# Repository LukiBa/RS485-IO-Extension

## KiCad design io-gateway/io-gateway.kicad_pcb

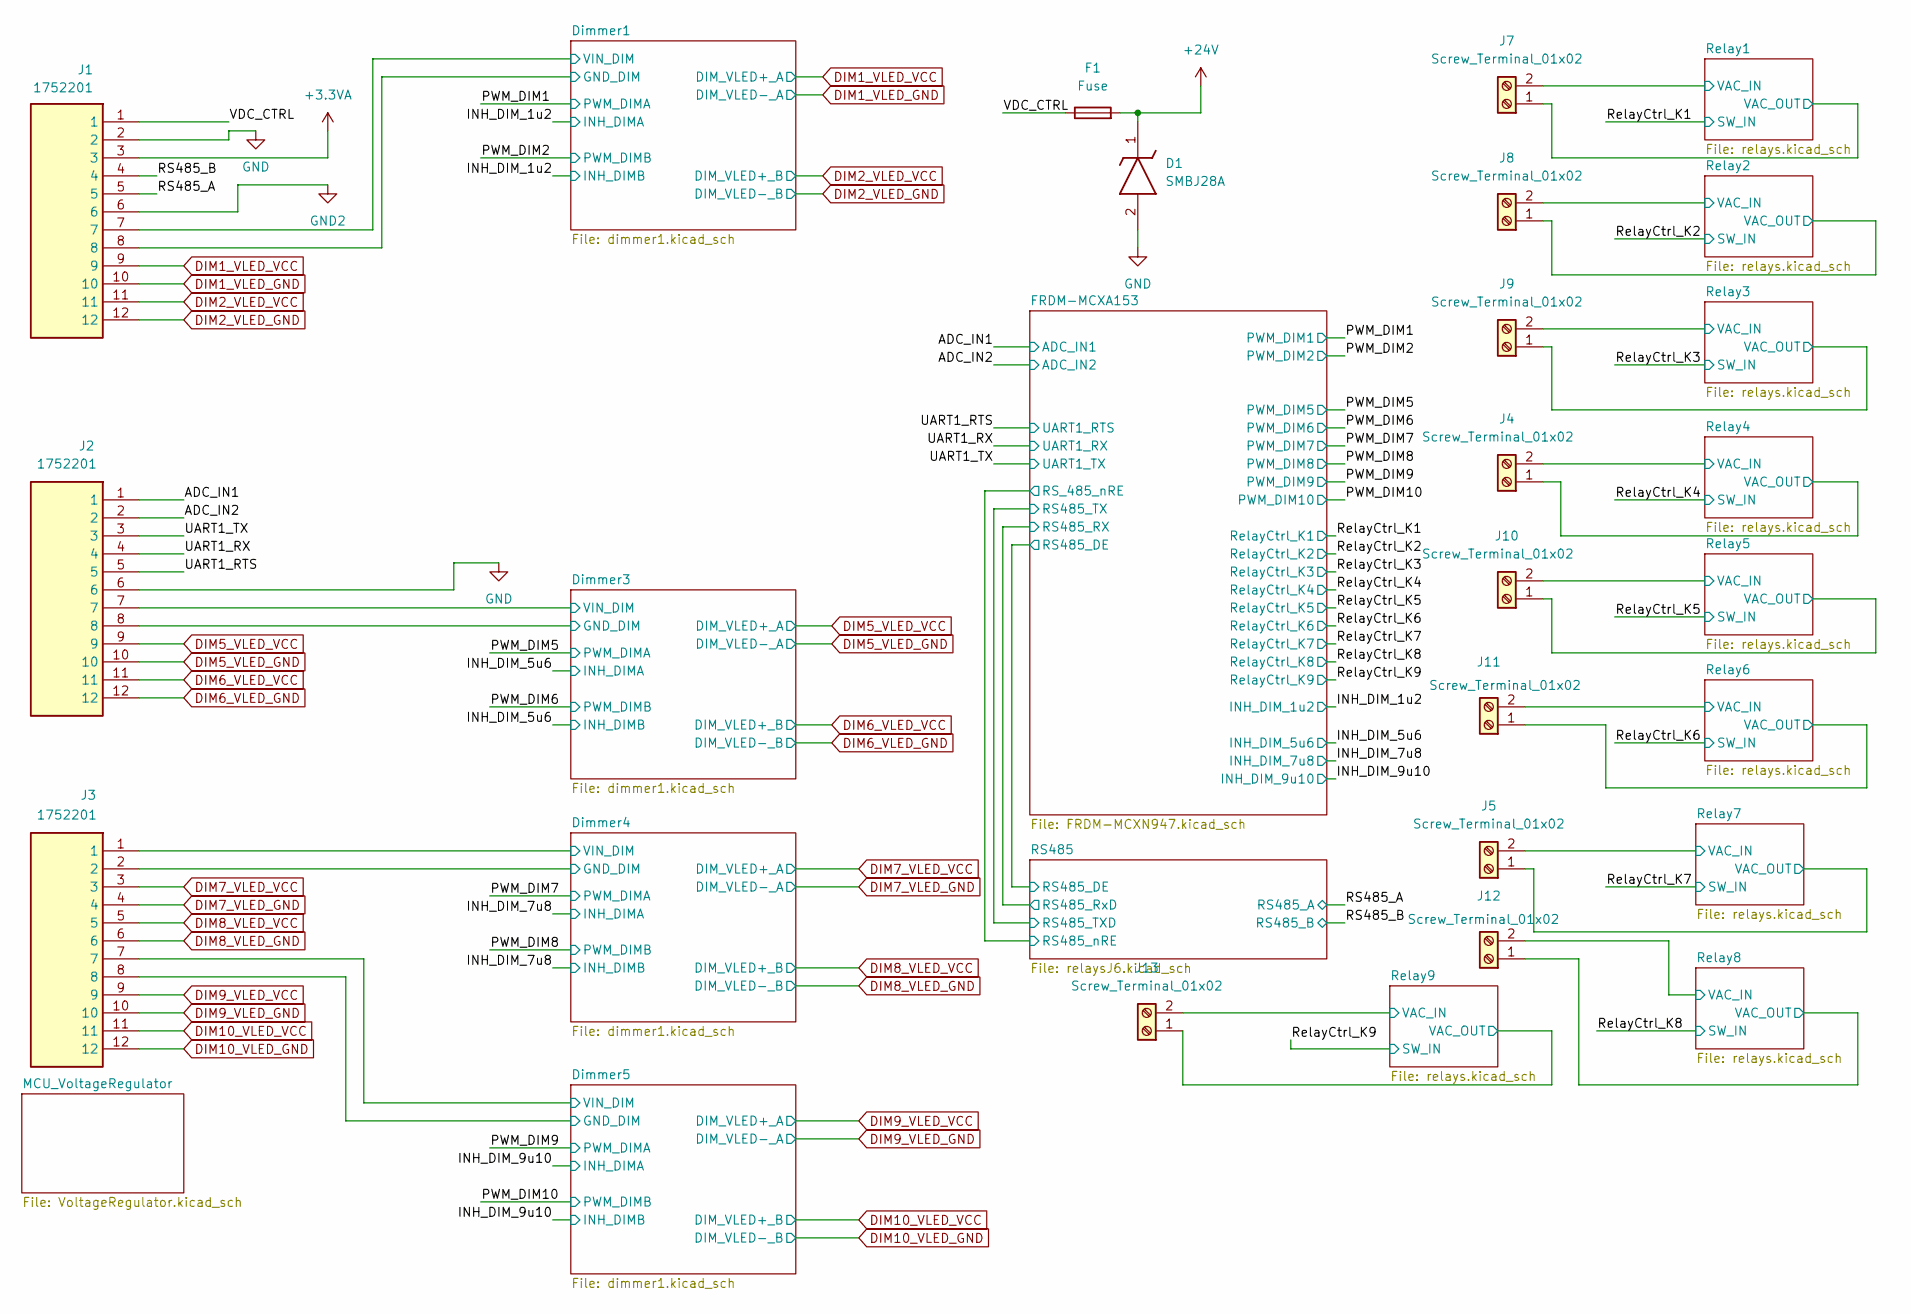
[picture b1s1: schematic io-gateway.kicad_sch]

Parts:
D1: SMBJ28A; DIOM5436X244N; Mouser Part Number 652-SMBJ28A
F1: Fuse; Fuse_1206_3216Metric_Pad1.42x1.75mm_HandSolder
J1, J2, J3: 1752201; Mouser Part Number 651-1752201
J4, J5, J7, J8, J9, J10, J11, J12, J13: Screw_Terminal_01x02; TerminalBlock_MaiXu_MX126-5.0-02P_1x02_P5.00mm

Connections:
+3.3VA: J1.3; also elsewhere on the board
+24V: D1.1 (K), F1.2; also elsewhere on the board
/ADC_IN1: J2.1; also elsewhere on the board
/ADC_IN2: J2.2; also elsewhere on the board
/Dimmer1/VIN_DIM: J1.7; also elsewhere on the board
/Dimmer3/VIN_DIM: J2.7; also elsewhere on the board
/Dimmer4/VIN_DIM: J3.1; also elsewhere on the board
/Dimmer5/VIN_DIM: J3.7; also elsewhere on the board
/RS485_A: J1.5; also elsewhere on the board
/RS485_B: J1.4; also elsewhere on the board
/Relay1/VAC_IN: J7.2; also elsewhere on the board
/Relay1/VAC_OUT: J7.1; also elsewhere on the board
/Relay2/VAC_IN: J8.2; also elsewhere on the board
/Relay2/VAC_OUT: J8.1; also elsewhere on the board
/Relay3/VAC_IN: J9.2; also elsewhere on the board
/Relay3/VAC_OUT: J9.1; also elsewhere on the board
/Relay4/VAC_IN: J4.2; also elsewhere on the board
/Relay4/VAC_OUT: J4.1; also elsewhere on the board
/Relay5/VAC_IN: J10.2; also elsewhere on the board
/Relay5/VAC_OUT: J10.1; also elsewhere on the board
/Relay6/VAC_IN: J11.2; also elsewhere on the board
/Relay6/VAC_OUT: J11.1; also elsewhere on the board
/Relay7/VAC_IN: J5.2; also elsewhere on the board
/Relay7/VAC_OUT: J5.1; also elsewhere on the board
/Relay8/VAC_IN: J12.2; also elsewhere on the board
/Relay8/VAC_OUT: J12.1; also elsewhere on the board
/Relay9/VAC_IN: J13.2; also elsewhere on the board
/Relay9/VAC_OUT: J13.1; also elsewhere on the board
/UART1_RTS: J2.5; also elsewhere on the board
/UART1_RX: J2.4; also elsewhere on the board
/UART1_TX: J2.3; also elsewhere on the board
/VDC_CTRL: F1.1, J1.1
DIM1_VLED_GND: J1.10; also elsewhere on the board
DIM1_VLED_VCC: J1.9; also elsewhere on the board
DIM2_VLED_GND: J1.12; also elsewhere on the board
DIM2_VLED_VCC: J1.11; also elsewhere on the board
DIM5_VLED_GND: J2.10; also elsewhere on the board
DIM5_VLED_VCC: J2.9; also elsewhere on the board
DIM6_VLED_GND: J2.12; also elsewhere on the board
DIM6_VLED_VCC: J2.11; also elsewhere on the board
DIM7_VLED_GND: J3.4; also elsewhere on the board
DIM7_VLED_VCC: J3.3; also elsewhere on the board
DIM8_VLED_GND: J3.6; also elsewhere on the board
DIM8_VLED_VCC: J3.5; also elsewhere on the board
DIM9_VLED_GND: J3.10; also elsewhere on the board
DIM9_VLED_VCC: J3.9; also elsewhere on the board
DIM10_VLED_GND: J3.12; also elsewhere on the board
DIM10_VLED_VCC: J3.11; also elsewhere on the board
GND: D1.2 (A), J1.2, J1.8, J2.6, J2.8, J3.2, J3.8; also elsewhere on the board
GND2: J1.6; also elsewhere on the board

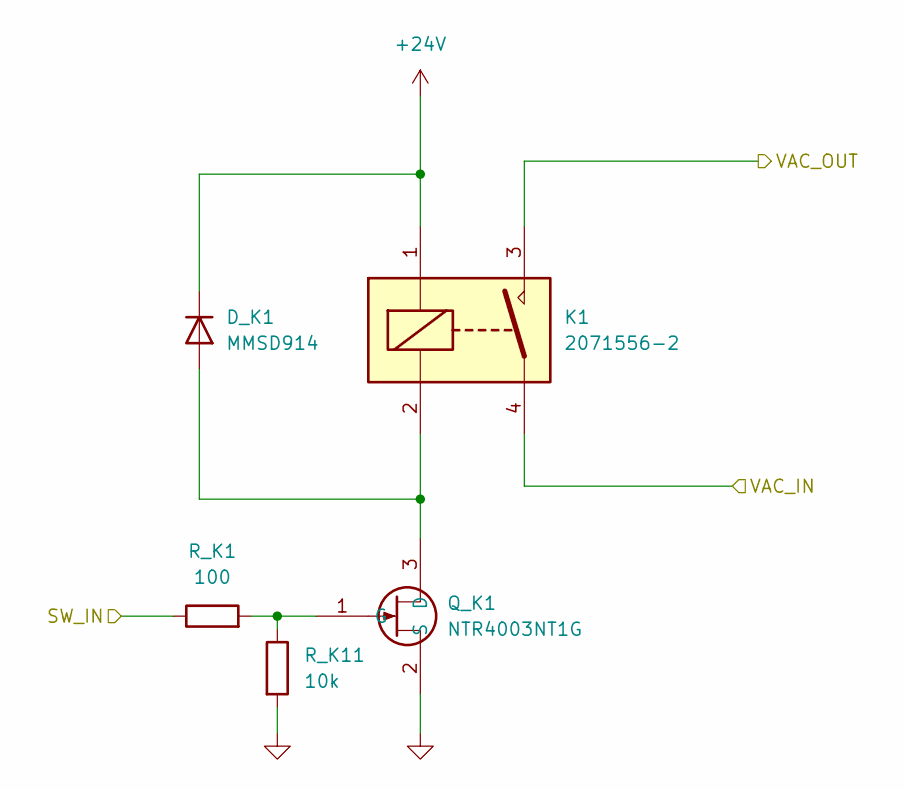
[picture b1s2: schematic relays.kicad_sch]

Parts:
D_K1: MMSD914; D_SOD-123
K1: 2071556-2; 20715562; Mouser Part Number 655-2071556-2
Q_K1: NTR4003NT1G; SOT-23-3; Mouser Part Number 863-NTR4003NT1G
R_K1: 100; R_0603_1608Metric_Pad0.98x0.95mm_HandSolder
R_K11: 10k; R_0603_1608Metric_Pad0.98x0.95mm_HandSolder

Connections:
+24V: D_K1.1 (K), K1.1 (COIL_1); also elsewhere on the board
/Relay1/VAC_IN: K1.4 (NO); also elsewhere on the board
/Relay1/VAC_OUT: K1.3 (COM); also elsewhere on the board
/RelayCtrl_K1: R_K1.1; also elsewhere on the board
GND: Q_K1.2 (S), R_K11.2; also elsewhere on the board
unnamed: D_K1.2 (A), K1.2 (COIL_2), Q_K1.3 (D)
unnamed: Q_K1.1 (G), R_K1.2, R_K11.1

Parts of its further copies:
D_K2, D_K3, D_K4, D_K5, D_K6, D_K7, D_K8, D_K9: MMSD914; D_SOD-123
K2, K3, K4, K5, K6, K7, K8, K9: 2071556-2; 20715562; Mouser Part Number 655-2071556-2
Q_K2, Q_K3, Q_K4, Q_K5, Q_K6, Q_K7, Q_K8, Q_K9: NTR4003NT1G; SOT-23-3; Mouser Part Number 863-NTR4003NT1G
R_K2, R_K3, R_K4, R_K5, R_K6, R_K7, R_K8, R_K9: 100; R_0603_1608Metric_Pad0.98x0.95mm_HandSolder
R_K12, R_K13, R_K14, R_K15, R_K16, R_K17, R_K18, R_K19: 10k; R_0603_1608Metric_Pad0.98x0.95mm_HandSolder

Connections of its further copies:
+24V: D_K2.1 (K), D_K3.1 (K), D_K4.1 (K), D_K5.1 (K), D_K6.1 (K), D_K7.1 (K), D_K8.1 (K), D_K9.1 (K), K2.1 (COIL_1), K3.1 (COIL_1), K4.1 (COIL_1), K5.1 (COIL_1), K6.1 (COIL_1), K7.1 (COIL_1), K8.1 (COIL_1), K9.1 (COIL_1); also elsewhere on the board
/Relay2/VAC_IN: K2.4 (NO); also elsewhere on the board
/Relay2/VAC_OUT: K2.3 (COM); also elsewhere on the board
/Relay3/VAC_IN: K3.4 (NO); also elsewhere on the board
/Relay3/VAC_OUT: K3.3 (COM); also elsewhere on the board
/Relay4/VAC_IN: K4.4 (NO); also elsewhere on the board
/Relay4/VAC_OUT: K4.3 (COM); also elsewhere on the board
/Relay5/VAC_IN: K5.4 (NO); also elsewhere on the board
/Relay5/VAC_OUT: K5.3 (COM); also elsewhere on the board
/Relay6/VAC_IN: K6.4 (NO); also elsewhere on the board
/Relay6/VAC_OUT: K6.3 (COM); also elsewhere on the board
/Relay7/VAC_IN: K7.4 (NO); also elsewhere on the board
/Relay7/VAC_OUT: K7.3 (COM); also elsewhere on the board
/Relay8/VAC_IN: K8.4 (NO); also elsewhere on the board
/Relay8/VAC_OUT: K8.3 (COM); also elsewhere on the board
/Relay9/VAC_IN: K9.4 (NO); also elsewhere on the board
/Relay9/VAC_OUT: K9.3 (COM); also elsewhere on the board
/RelayCtrl_K2: R_K2.1; also elsewhere on the board
/RelayCtrl_K3: R_K3.1; also elsewhere on the board
/RelayCtrl_K4: R_K4.1; also elsewhere on the board
/RelayCtrl_K5: R_K5.1; also elsewhere on the board
/RelayCtrl_K6: R_K6.1; also elsewhere on the board
/RelayCtrl_K7: R_K7.1; also elsewhere on the board
/RelayCtrl_K8: R_K8.1; also elsewhere on the board
/RelayCtrl_K9: R_K9.1; also elsewhere on the board
GND: Q_K2.2 (S), Q_K3.2 (S), Q_K4.2 (S), Q_K5.2 (S), Q_K6.2 (S), Q_K7.2 (S), Q_K8.2 (S), Q_K9.2 (S), R_K12.2, R_K13.2, R_K14.2, R_K15.2, R_K16.2, R_K17.2, R_K18.2, R_K19.2; also elsewhere on the board
unnamed: D_K2.2 (A), K2.2 (COIL_2), Q_K2.3 (D)
unnamed: D_K3.2 (A), K3.2 (COIL_2), Q_K3.3 (D)
unnamed: D_K4.2 (A), K4.2 (COIL_2), Q_K4.3 (D)
unnamed: D_K5.2 (A), K5.2 (COIL_2), Q_K5.3 (D)
unnamed: D_K6.2 (A), K6.2 (COIL_2), Q_K6.3 (D)
unnamed: D_K7.2 (A), K7.2 (COIL_2), Q_K7.3 (D)
unnamed: D_K8.2 (A), K8.2 (COIL_2), Q_K8.3 (D)
unnamed: D_K9.2 (A), K9.2 (COIL_2), Q_K9.3 (D)
unnamed: Q_K2.1 (G), R_K2.2, R_K12.1
unnamed: Q_K3.1 (G), R_K3.2, R_K13.1
unnamed: Q_K4.1 (G), R_K4.2, R_K14.1
unnamed: Q_K5.1 (G), R_K5.2, R_K15.1
unnamed: Q_K6.1 (G), R_K6.2, R_K16.1
unnamed: Q_K7.1 (G), R_K7.2, R_K17.1
unnamed: Q_K8.1 (G), R_K8.2, R_K18.1
unnamed: Q_K9.1 (G), R_K9.2, R_K19.1

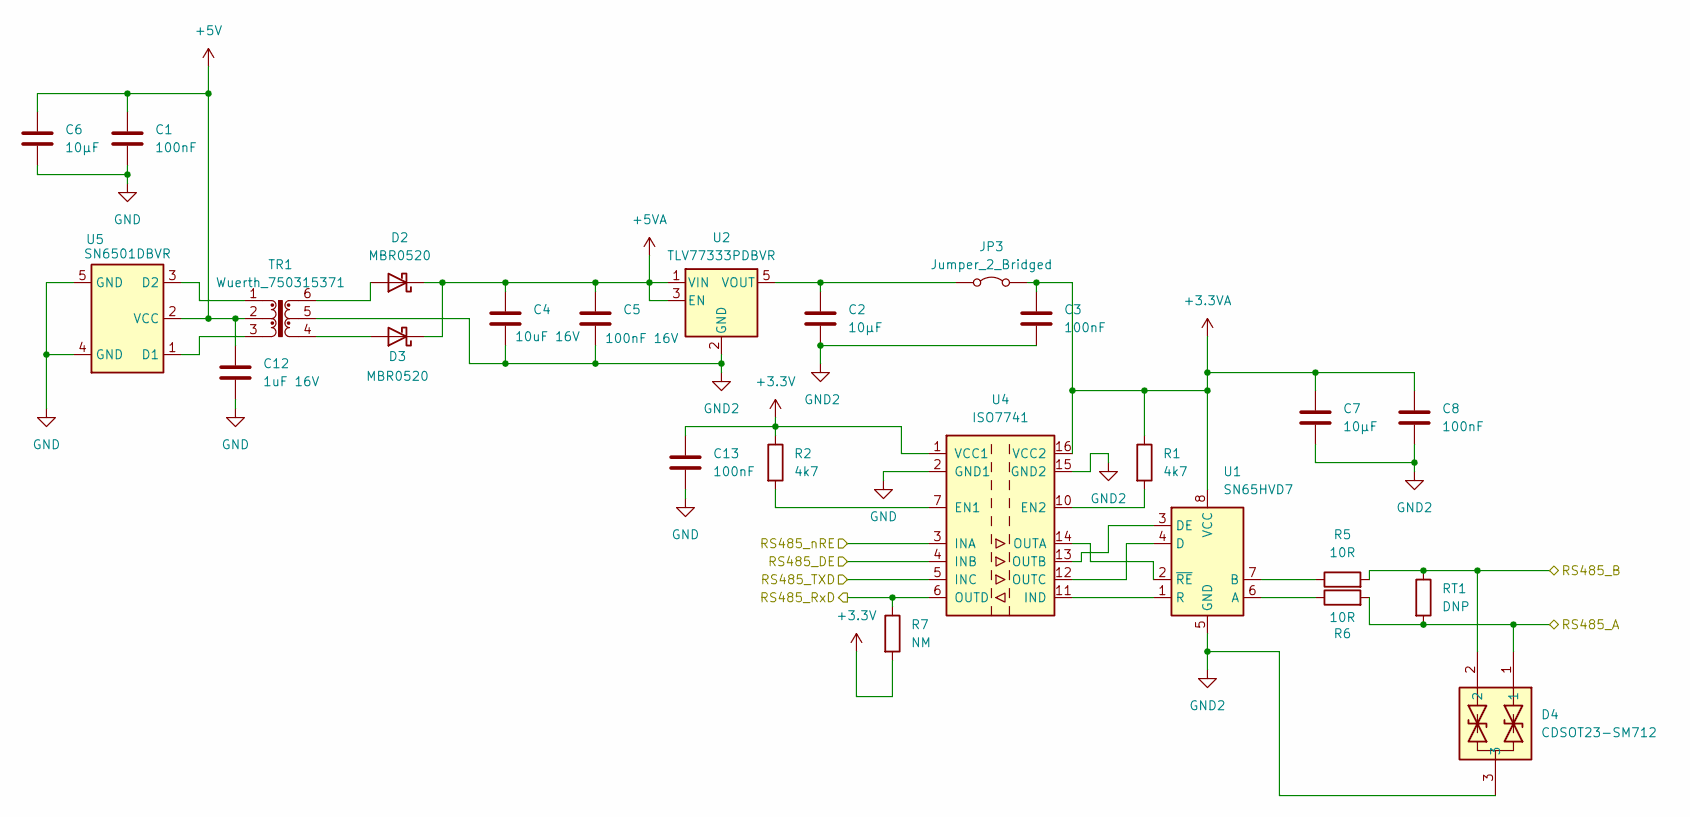
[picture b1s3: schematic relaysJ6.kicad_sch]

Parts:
C1, C3, C8, C13: 100nF; C_0603_1608Metric_Pad1.08x0.95mm_HandSolder
C2, C6, C7: 10µF; C_0603_1608Metric_Pad1.08x0.95mm_HandSolder
C4: 10uF 16V; C_0603_1608Metric_Pad1.08x0.95mm_HandSolder
C5: 100nF 16V; C_0603_1608Metric_Pad1.08x0.95mm_HandSolder
C12: 1uF 16V; C_0603_1608Metric_Pad1.08x0.95mm_HandSolder
D2, D3: MBR0520; D_SOD-123
D4: CDSOT23-SM712; SOT95P230X117-3N; Mouser Part Number 652-CDSOT23-SM712
JP3: Jumper_2_Bridged; PinHeader_1x02_P2.54mm_Vertical
R1, R2: 4k7; R_0603_1608Metric_Pad0.98x0.95mm_HandSolder
R5, R6: 10R; R_0603_1608Metric_Pad0.98x0.95mm_HandSolder
R7: NM; R_0603_1608Metric_Pad0.98x0.95mm_HandSolder
RT1: DNP; R_0603_1608Metric_Pad0.98x0.95mm_HandSolder
TR1: Wuerth_750315371; Transformer_Wuerth_750315371
U1: SN65HVD7; SOIC-8_3.9x4.9mm_P1.27mm
U2: TLV77333PDBVR; SOT-23-5
U4: ISO7741; SOIC-16W_7.5x10.3mm_P1.27mm
U5: SN6501DBVR; SOT-23-5

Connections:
+3.3V: C13.1, R2.1, R7.2, U4.1 (VCC1); also elsewhere on the board
+3.3VA: C3.1, C7.1, C8.1, JP3.2 (B), R1.1, U1.8 (VCC), U4.16 (VCC2); also elsewhere on the board
+5V: C1.1, C6.1, C12.1, TR1.2, U5.2 (VCC); also elsewhere on the board
+5VA: C4.1, C5.1, D2.1 (K), D3.1 (K), U2.1 (VIN), U2.3 (EN)
/FRDM-MCXA153/RS485_DE: U4.4 (INB); also elsewhere on the board
/FRDM-MCXA153/RS485_RX: R7.1, U4.6 (OUTD); also elsewhere on the board
/FRDM-MCXA153/RS485_TX: U4.5 (INC); also elsewhere on the board
/FRDM-MCXA153/RS_485_nRE: U4.3 (INA); also elsewhere on the board
/RS485_A: D4.1, R6.2, RT1.2; also elsewhere on the board
/RS485_B: D4.2, R5.2, RT1.1; also elsewhere on the board
GND: C1.2, C6.2, C12.2, C13.2, U4.2 (GND1), U4.8 (GND1), U5.4 (GND), U5.5 (GND); also elsewhere on the board
GND2: C2.2, C3.2, C4.2, C5.2, C7.2, C8.2, D4.3, TR1.5, U1.5 (GND), U2.2 (GND), U4.9 (GND2), U4.15 (GND2); also elsewhere on the board
unnamed: D2.2 (A), TR1.6
unnamed: D3.2 (A), TR1.4
unnamed: C2.1, JP3.1 (A), U2.5 (VOUT)
unnamed: R6.1, U1.6 (A)
unnamed: R5.1, U1.7 (B)
unnamed: U1.4 (D), U4.12 (OUTC)
unnamed: U1.3 (DE), U4.13 (OUTB)
unnamed: U1.1 (R), U4.11 (IND)
unnamed: U1.2 (~RE), U4.14 (OUTA)
unnamed: R2.2, U4.7 (EN1)
unnamed: R1.2, U4.10 (EN2)
unnamed: TR1.3, U5.1 (D1)
unnamed: TR1.1, U5.3 (D2)

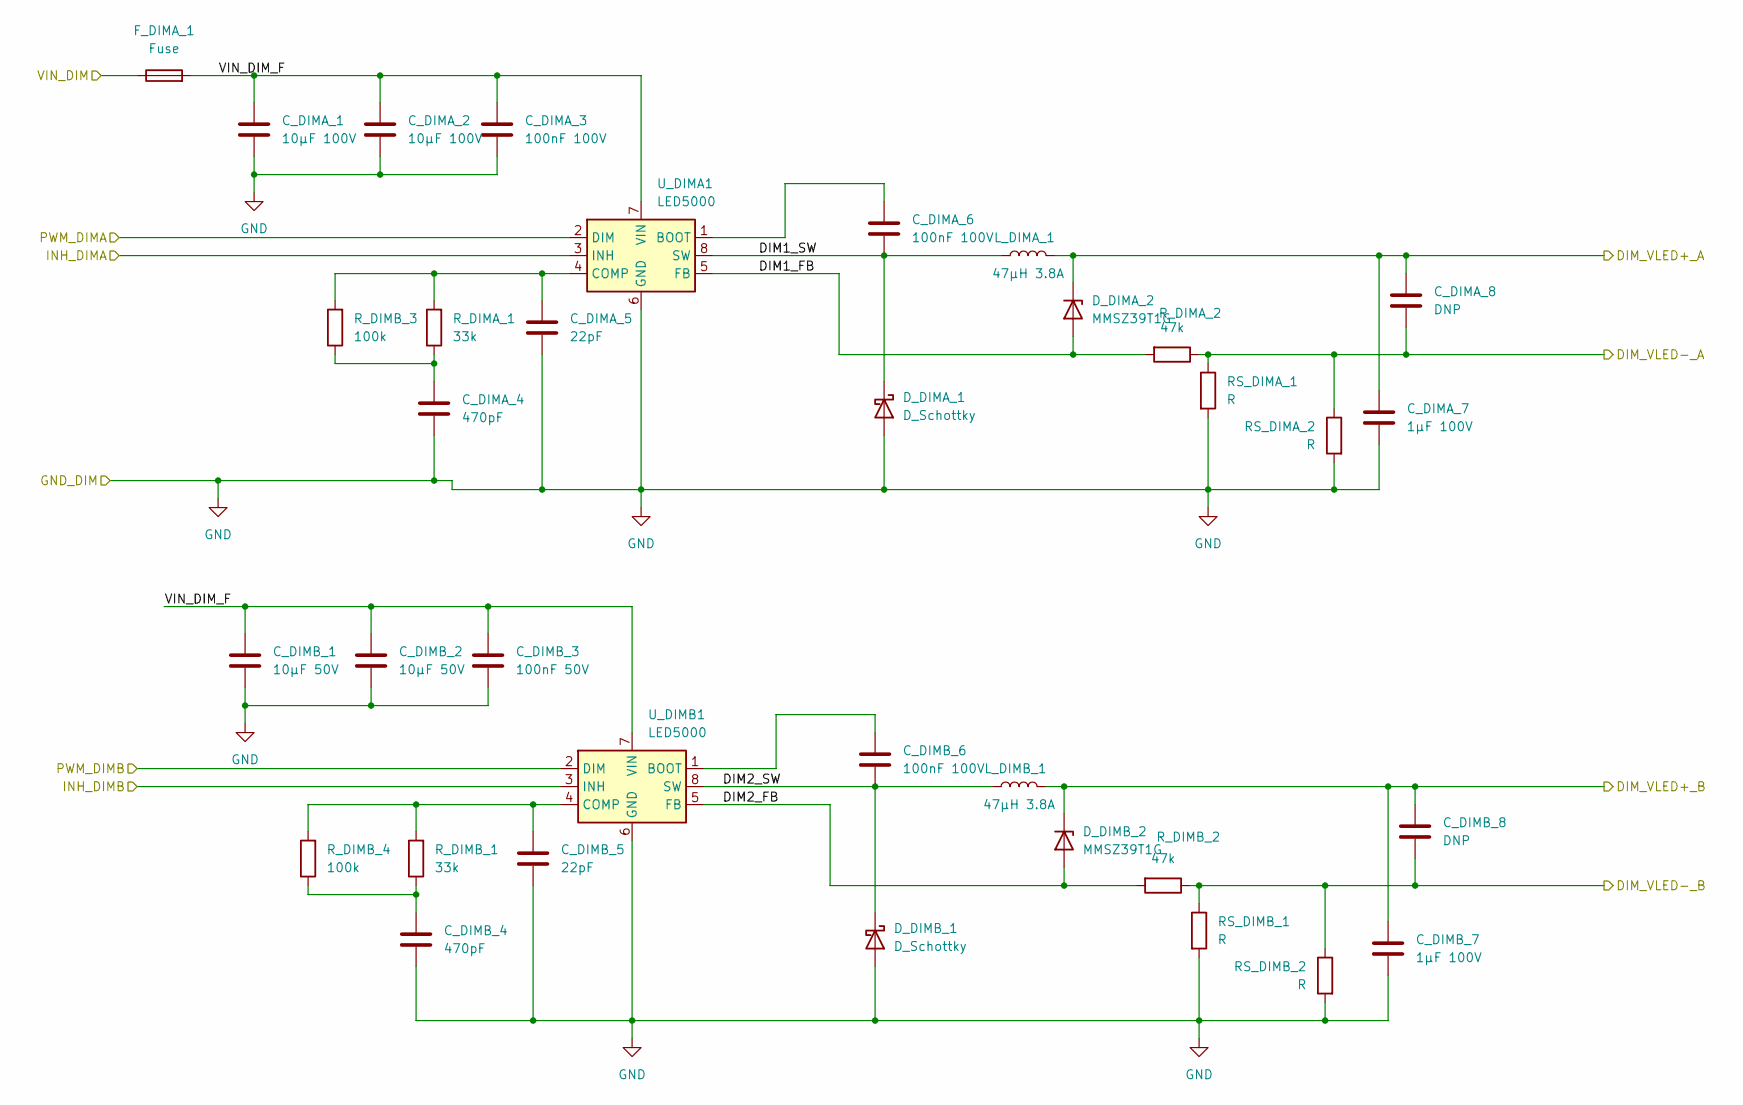
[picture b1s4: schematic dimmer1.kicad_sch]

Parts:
C_DIMA_1, C_DIMA_2: 10µF 100V; C_1210_3225Metric_Pad1.33x2.70mm_HandSolder
C_DIMA_3, C_DIMA_6: 100nF 100V; C_0603_1608Metric_Pad1.08x0.95mm_HandSolder
C_DIMA_4: 470pF; C_0603_1608Metric_Pad1.08x0.95mm_HandSolder
C_DIMA_5: 22pF; C_0603_1608Metric_Pad1.08x0.95mm_HandSolder
C_DIMA_7: 1µF 100V; C_1206_3216Metric_Pad1.33x1.80mm_HandSolder
C_DIMA_8: DNP; C_1206_3216Metric_Pad1.33x1.80mm_HandSolder
C_DIMB_1, C_DIMB_2: 10µF 50V; C_1210_3225Metric_Pad1.33x2.70mm_HandSolder
C_DIMB_3: 100nF 50V; C_0603_1608Metric_Pad1.08x0.95mm_HandSolder
C_DIMB_4: 470pF; C_0603_1608Metric_Pad1.08x0.95mm_HandSolder
C_DIMB_5: 22pF; C_0603_1608Metric_Pad1.08x0.95mm_HandSolder
C_DIMB_6: 100nF 100V; C_0603_1608Metric_Pad1.08x0.95mm_HandSolder
C_DIMB_7: 1µF 100V; C_1206_3216Metric_Pad1.33x1.80mm_HandSolder
C_DIMB_8: DNP; C_1206_3216Metric_Pad1.33x1.80mm_HandSolder
D_DIMA_1: D_Schottky; D_SMB_Handsoldering
D_DIMA_2: MMSZ39T1G; D_SOD-123
D_DIMB_1: D_Schottky; D_SMB
D_DIMB_2: MMSZ39T1G; D_SOD-123
F_DIMA_1: Fuse; Fuse_1206_3216Metric_Pad1.42x1.75mm_HandSolder
L_DIMA_1: 47µH 3.8A; L_12x12mm_H8mm
L_DIMB_1: 47µH 3.8A; L_12x12mm_H8mm
RS_DIMA_1, RS_DIMA_2: R; R_1206_3216Metric_Pad1.30x1.75mm_HandSolder
RS_DIMB_1, RS_DIMB_2: R; R_1206_3216Metric_Pad1.30x1.75mm_HandSolder
R_DIMA_1: 33k; R_0603_1608Metric_Pad0.98x0.95mm_HandSolder
R_DIMA_2: 47k; R_0603_1608Metric_Pad0.98x0.95mm_HandSolder
R_DIMB_1: 33k; R_0603_1608Metric_Pad0.98x0.95mm_HandSolder
R_DIMB_2: 47k; R_0603_1608Metric_Pad0.98x0.95mm_HandSolder
R_DIMB_3, R_DIMB_4: 100k; R_0603_1608Metric_Pad0.98x0.95mm_HandSolder
U_DIMA1: LED5000; HSOP-8-1EP_3.9x4.9mm_P1.27mm_EP2.41x3.1mm
U_DIMB1: LED5000; HSOP-8-1EP_3.9x4.9mm_P1.27mm_EP2.41x3.1mm

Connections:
/Dimmer1/DIM1_FB: D_DIMA_2.2 (A), R_DIMA_2.2, U_DIMA1.5 (FB)
/Dimmer1/DIM1_SW: C_DIMA_6.2, D_DIMA_1.1 (K), L_DIMA_1.2, U_DIMA1.8 (SW)
/Dimmer1/DIM2_FB: D_DIMB_2.2 (A), R_DIMB_2.2, U_DIMB1.5 (FB)
/Dimmer1/DIM2_SW: C_DIMB_6.2, D_DIMB_1.1 (K), L_DIMB_1.2, U_DIMB1.8 (SW)
/Dimmer1/VIN_DIM: F_DIMA_1.1; also elsewhere on the board
/Dimmer1/VIN_DIM_F: C_DIMA_1.1, C_DIMA_2.1, C_DIMA_3.1, C_DIMB_1.1, C_DIMB_2.1, C_DIMB_3.1, F_DIMA_1.2, U_DIMA1.7 (VIN), U_DIMB1.7 (VIN)
/INH_DIM_1u2: U_DIMA1.3 (INH), U_DIMB1.3 (INH); also elsewhere on the board
/PWM_DIM1: U_DIMA1.2 (DIM); also elsewhere on the board
/PWM_DIM2: U_DIMB1.2 (DIM); also elsewhere on the board
DIM1_VLED_GND: C_DIMA_8.2, RS_DIMA_1.1, RS_DIMA_2.1, R_DIMA_2.1; also elsewhere on the board
DIM1_VLED_VCC: C_DIMA_7.1, C_DIMA_8.1, D_DIMA_2.1 (K), L_DIMA_1.1; also elsewhere on the board
DIM2_VLED_GND: C_DIMB_8.2, RS_DIMB_1.1, RS_DIMB_2.1, R_DIMB_2.1; also elsewhere on the board
DIM2_VLED_VCC: C_DIMB_7.1, C_DIMB_8.1, D_DIMB_2.1 (K), L_DIMB_1.1; also elsewhere on the board
GND: C_DIMA_1.2, C_DIMA_2.2, C_DIMA_3.2, C_DIMA_4.2, C_DIMA_5.2, C_DIMA_7.2, C_DIMB_1.2, C_DIMB_2.2, C_DIMB_3.2, C_DIMB_4.2, C_DIMB_5.2, C_DIMB_7.2, D_DIMA_1.2 (A), D_DIMB_1.2 (A), RS_DIMA_1.2, RS_DIMA_2.2, RS_DIMB_1.2, RS_DIMB_2.2, U_DIMA1.6 (GND), U_DIMA1.9 (GND), U_DIMB1.6 (GND), U_DIMB1.9 (GND); also elsewhere on the board
unnamed: C_DIMA_4.1, R_DIMA_1.1, R_DIMB_3.1
unnamed: C_DIMB_4.1, R_DIMB_1.1, R_DIMB_4.1
unnamed: C_DIMA_6.1, U_DIMA1.1 (BOOT)
unnamed: C_DIMA_5.1, R_DIMA_1.2, R_DIMB_3.2, U_DIMA1.4 (COMP)
unnamed: C_DIMB_6.1, U_DIMB1.1 (BOOT)
unnamed: C_DIMB_5.1, R_DIMB_1.2, R_DIMB_4.2, U_DIMB1.4 (COMP)

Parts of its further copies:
C_DIMA_17, C_DIMA_18, C_DIMA_25, C_DIMA_26, C_DIMA_33, C_DIMA_34: 10µF 100V; C_1210_3225Metric_Pad1.33x2.70mm_HandSolder
C_DIMA_19, C_DIMA_27, C_DIMA_35: 470pF; C_0603_1608Metric_Pad1.08x0.95mm_HandSolder
C_DIMA_20, C_DIMA_22, C_DIMA_28, C_DIMA_30, C_DIMA_36, C_DIMA_38: 100nF 100V; C_0603_1608Metric_Pad1.08x0.95mm_HandSolder
C_DIMA_21, C_DIMA_29, C_DIMA_37: 22pF; C_0603_1608Metric_Pad1.08x0.95mm_HandSolder
C_DIMA_23, C_DIMA_31, C_DIMA_39: 1µF 100V; C_1206_3216Metric_Pad1.33x1.80mm_HandSolder
C_DIMA_24, C_DIMA_32, C_DIMA_40: DNP; C_1206_3216Metric_Pad1.33x1.80mm_HandSolder
C_DIMB_17, C_DIMB_18, C_DIMB_25, C_DIMB_26, C_DIMB_33, C_DIMB_34: 10µF 50V; C_1210_3225Metric_Pad1.33x2.70mm_HandSolder
C_DIMB_19, C_DIMB_27, C_DIMB_35: 470pF; C_0603_1608Metric_Pad1.08x0.95mm_HandSolder
C_DIMB_20, C_DIMB_28, C_DIMB_36: 100nF 50V; C_0603_1608Metric_Pad1.08x0.95mm_HandSolder
C_DIMB_21, C_DIMB_29, C_DIMB_37: 22pF; C_0603_1608Metric_Pad1.08x0.95mm_HandSolder
C_DIMB_22, C_DIMB_30, C_DIMB_38: 100nF 100V; C_0603_1608Metric_Pad1.08x0.95mm_HandSolder
C_DIMB_23, C_DIMB_31, C_DIMB_39: 1µF 100V; C_1206_3216Metric_Pad1.33x1.80mm_HandSolder
C_DIMB_24, C_DIMB_32, C_DIMB_40: DNP; C_1206_3216Metric_Pad1.33x1.80mm_HandSolder
D_DIMA_5, D_DIMA_7, D_DIMA_9: D_Schottky; D_SMB_Handsoldering
D_DIMA_6, D_DIMA_8, D_DIMA_10: MMSZ39T1G; D_SOD-123
D_DIMB_5, D_DIMB_7, D_DIMB_9: D_Schottky; D_SMB
D_DIMB_6, D_DIMB_8, D_DIMB_10: MMSZ39T1G; D_SOD-123
F_DIMA_3, F_DIMA_4, F_DIMA_5: Fuse; Fuse_1206_3216Metric_Pad1.42x1.75mm_HandSolder
L_DIMA_3, L_DIMA_4, L_DIMA_5: 47µH 3.8A; L_12x12mm_H8mm
L_DIMB_3, L_DIMB_4, L_DIMB_5: 47µH 3.8A; L_12x12mm_H8mm
RS_DIMA_3, RS_DIMA_4, RS_DIMA_5, RS_DIMA_6, RS_DIMA_7, RS_DIMA_8: R; R_1206_3216Metric_Pad1.30x1.75mm_HandSolder
RS_DIMB_3, RS_DIMB_4, RS_DIMB_5, RS_DIMB_6, RS_DIMB_7, RS_DIMB_8: R; R_1206_3216Metric_Pad1.30x1.75mm_HandSolder
R_DIMA_5, R_DIMA_7, R_DIMA_9: 33k; R_0603_1608Metric_Pad0.98x0.95mm_HandSolder
R_DIMA_6, R_DIMA_8, R_DIMA_10: 47k; R_0603_1608Metric_Pad0.98x0.95mm_HandSolder
R_DIMB_5, R_DIMB_7, R_DIMB_9: 33k; R_0603_1608Metric_Pad0.98x0.95mm_HandSolder
R_DIMB_6, R_DIMB_8, R_DIMB_10: 47k; R_0603_1608Metric_Pad0.98x0.95mm_HandSolder
R_DIMB_11, R_DIMB_12, R_DIMB_13, R_DIMB_32, R_DIMB_33, R_DIMB_34: 100k; R_0603_1608Metric_Pad0.98x0.95mm_HandSolder
U_DIMA3, U_DIMA4, U_DIMA5: LED5000; HSOP-8-1EP_3.9x4.9mm_P1.27mm_EP2.41x3.1mm
U_DIMB3, U_DIMB4, U_DIMB5: LED5000; HSOP-8-1EP_3.9x4.9mm_P1.27mm_EP2.41x3.1mm

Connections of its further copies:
/Dimmer3/DIM1_FB: D_DIMA_6.2 (A), R_DIMA_6.2, U_DIMA3.5 (FB)
/Dimmer3/DIM1_SW: C_DIMA_22.2, D_DIMA_5.1 (K), L_DIMA_3.2, U_DIMA3.8 (SW)
/Dimmer3/DIM2_FB: D_DIMB_6.2 (A), R_DIMB_6.2, U_DIMB3.5 (FB)
/Dimmer3/DIM2_SW: C_DIMB_22.2, D_DIMB_5.1 (K), L_DIMB_3.2, U_DIMB3.8 (SW)
/Dimmer3/VIN_DIM: F_DIMA_3.1; also elsewhere on the board
/Dimmer3/VIN_DIM_F: C_DIMA_17.1, C_DIMA_18.1, C_DIMA_20.1, C_DIMB_17.1, C_DIMB_18.1, C_DIMB_20.1, F_DIMA_3.2, U_DIMA3.7 (VIN), U_DIMB3.7 (VIN)
/Dimmer4/DIM1_FB: D_DIMA_8.2 (A), R_DIMA_8.2, U_DIMA4.5 (FB)
/Dimmer4/DIM1_SW: C_DIMA_30.2, D_DIMA_7.1 (K), L_DIMA_4.2, U_DIMA4.8 (SW)
/Dimmer4/DIM2_FB: D_DIMB_8.2 (A), R_DIMB_8.2, U_DIMB4.5 (FB)
/Dimmer4/DIM2_SW: C_DIMB_30.2, D_DIMB_7.1 (K), L_DIMB_4.2, U_DIMB4.8 (SW)
/Dimmer4/VIN_DIM: F_DIMA_4.1; also elsewhere on the board
/Dimmer4/VIN_DIM_F: C_DIMA_25.1, C_DIMA_26.1, C_DIMA_28.1, C_DIMB_25.1, C_DIMB_26.1, C_DIMB_28.1, F_DIMA_4.2, U_DIMA4.7 (VIN), U_DIMB4.7 (VIN)
/Dimmer5/DIM1_FB: D_DIMA_10.2 (A), R_DIMA_10.2, U_DIMA5.5 (FB)
/Dimmer5/DIM1_SW: C_DIMA_38.2, D_DIMA_9.1 (K), L_DIMA_5.2, U_DIMA5.8 (SW)
/Dimmer5/DIM2_FB: D_DIMB_10.2 (A), R_DIMB_10.2, U_DIMB5.5 (FB)
/Dimmer5/DIM2_SW: C_DIMB_38.2, D_DIMB_9.1 (K), L_DIMB_5.2, U_DIMB5.8 (SW)
/Dimmer5/VIN_DIM: F_DIMA_5.1; also elsewhere on the board
/Dimmer5/VIN_DIM_F: C_DIMA_33.1, C_DIMA_34.1, C_DIMA_36.1, C_DIMB_33.1, C_DIMB_34.1, C_DIMB_36.1, F_DIMA_5.2, U_DIMA5.7 (VIN), U_DIMB5.7 (VIN)
/INH_DIM_5u6: U_DIMA3.3 (INH), U_DIMB3.3 (INH); also elsewhere on the board
/INH_DIM_7u8: U_DIMA4.3 (INH), U_DIMB4.3 (INH); also elsewhere on the board
/INH_DIM_9u10: U_DIMA5.3 (INH), U_DIMB5.3 (INH); also elsewhere on the board
/PWM_DIM5: U_DIMA3.2 (DIM); also elsewhere on the board
/PWM_DIM6: U_DIMB3.2 (DIM); also elsewhere on the board
/PWM_DIM7: U_DIMA4.2 (DIM); also elsewhere on the board
/PWM_DIM8: U_DIMB4.2 (DIM); also elsewhere on the board
/PWM_DIM9: U_DIMA5.2 (DIM); also elsewhere on the board
/PWM_DIM10: U_DIMB5.2 (DIM); also elsewhere on the board
DIM5_VLED_GND: C_DIMA_24.2, RS_DIMA_3.1, RS_DIMA_6.1, R_DIMA_6.1; also elsewhere on the board
DIM5_VLED_VCC: C_DIMA_23.1, C_DIMA_24.1, D_DIMA_6.1 (K), L_DIMA_3.1; also elsewhere on the board
DIM6_VLED_GND: C_DIMB_24.2, RS_DIMB_3.1, RS_DIMB_6.1, R_DIMB_6.1; also elsewhere on the board
DIM6_VLED_VCC: C_DIMB_23.1, C_DIMB_24.1, D_DIMB_6.1 (K), L_DIMB_3.1; also elsewhere on the board
DIM7_VLED_GND: C_DIMA_32.2, RS_DIMA_4.1, RS_DIMA_7.1, R_DIMA_8.1; also elsewhere on the board
DIM7_VLED_VCC: C_DIMA_31.1, C_DIMA_32.1, D_DIMA_8.1 (K), L_DIMA_4.1; also elsewhere on the board
DIM8_VLED_GND: C_DIMB_32.2, RS_DIMB_4.1, RS_DIMB_7.1, R_DIMB_8.1; also elsewhere on the board
DIM8_VLED_VCC: C_DIMB_31.1, C_DIMB_32.1, D_DIMB_8.1 (K), L_DIMB_4.1; also elsewhere on the board
DIM9_VLED_GND: C_DIMA_40.2, RS_DIMA_5.1, RS_DIMA_8.1, R_DIMA_10.1; also elsewhere on the board
DIM9_VLED_VCC: C_DIMA_39.1, C_DIMA_40.1, D_DIMA_10.1 (K), L_DIMA_5.1; also elsewhere on the board
DIM10_VLED_GND: C_DIMB_40.2, RS_DIMB_5.1, RS_DIMB_8.1, R_DIMB_10.1; also elsewhere on the board
DIM10_VLED_VCC: C_DIMB_39.1, C_DIMB_40.1, D_DIMB_10.1 (K), L_DIMB_5.1; also elsewhere on the board
GND: C_DIMA_17.2, C_DIMA_18.2, C_DIMA_19.2, C_DIMA_20.2, C_DIMA_21.2, C_DIMA_23.2, C_DIMA_25.2, C_DIMA_26.2, C_DIMA_27.2, C_DIMA_28.2, C_DIMA_29.2, C_DIMA_31.2, C_DIMA_33.2, C_DIMA_34.2, C_DIMA_35.2, C_DIMA_36.2, C_DIMA_37.2, C_DIMA_39.2, C_DIMB_17.2, C_DIMB_18.2, C_DIMB_19.2, C_DIMB_20.2, C_DIMB_21.2, C_DIMB_23.2, C_DIMB_25.2, C_DIMB_26.2, C_DIMB_27.2, C_DIMB_28.2, C_DIMB_29.2, C_DIMB_31.2, C_DIMB_33.2, C_DIMB_34.2, C_DIMB_35.2, C_DIMB_36.2, C_DIMB_37.2, C_DIMB_39.2, D_DIMA_5.2 (A), D_DIMA_7.2 (A), D_DIMA_9.2 (A), D_DIMB_5.2 (A), D_DIMB_7.2 (A), D_DIMB_9.2 (A), RS_DIMA_3.2, RS_DIMA_4.2, RS_DIMA_5.2, RS_DIMA_6.2, RS_DIMA_7.2, RS_DIMA_8.2, RS_DIMB_3.2, RS_DIMB_4.2, RS_DIMB_5.2, RS_DIMB_6.2, RS_DIMB_7.2, RS_DIMB_8.2, U_DIMA3.6 (GND), U_DIMA3.9 (GND), U_DIMA4.6 (GND), U_DIMA4.9 (GND), U_DIMA5.6 (GND), U_DIMA5.9 (GND), U_DIMB3.6 (GND), U_DIMB3.9 (GND), U_DIMB4.6 (GND), U_DIMB4.9 (GND), U_DIMB5.6 (GND), U_DIMB5.9 (GND); also elsewhere on the board
unnamed: C_DIMA_19.1, R_DIMA_5.1, R_DIMB_32.1
unnamed: C_DIMA_27.1, R_DIMA_7.1, R_DIMB_33.1
unnamed: C_DIMA_35.1, R_DIMA_9.1, R_DIMB_34.1
unnamed: C_DIMB_19.1, R_DIMB_5.1, R_DIMB_11.1
unnamed: C_DIMB_27.1, R_DIMB_7.1, R_DIMB_12.1
unnamed: C_DIMB_35.1, R_DIMB_9.1, R_DIMB_13.1
unnamed: C_DIMA_22.1, U_DIMA3.1 (BOOT)
unnamed: C_DIMA_21.1, R_DIMA_5.2, R_DIMB_32.2, U_DIMA3.4 (COMP)
unnamed: C_DIMA_30.1, U_DIMA4.1 (BOOT)
unnamed: C_DIMA_29.1, R_DIMA_7.2, R_DIMB_33.2, U_DIMA4.4 (COMP)
unnamed: C_DIMA_38.1, U_DIMA5.1 (BOOT)
unnamed: C_DIMA_37.1, R_DIMA_9.2, R_DIMB_34.2, U_DIMA5.4 (COMP)
unnamed: C_DIMB_22.1, U_DIMB3.1 (BOOT)
unnamed: C_DIMB_21.1, R_DIMB_5.2, R_DIMB_11.2, U_DIMB3.4 (COMP)
unnamed: C_DIMB_30.1, U_DIMB4.1 (BOOT)
unnamed: C_DIMB_29.1, R_DIMB_7.2, R_DIMB_12.2, U_DIMB4.4 (COMP)
unnamed: C_DIMB_38.1, U_DIMB5.1 (BOOT)
unnamed: C_DIMB_37.1, R_DIMB_9.2, R_DIMB_13.2, U_DIMB5.4 (COMP)

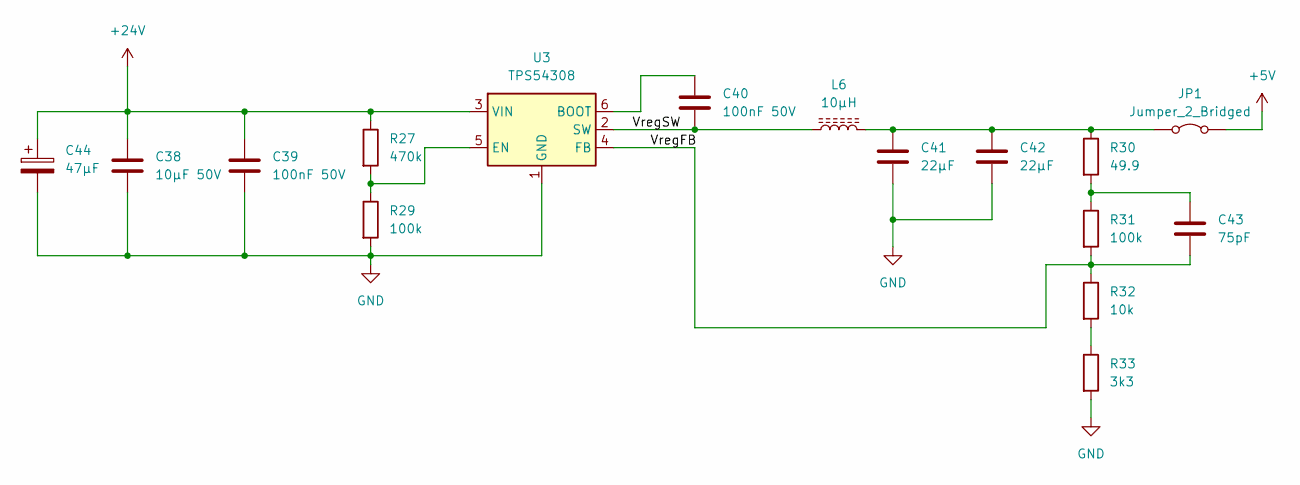
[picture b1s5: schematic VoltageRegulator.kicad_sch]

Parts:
C38: 10µF 50V; C_1210_3225Metric
C39, C40: 100nF 50V; C_0603_1608Metric
C41, C42: 22µF; C_0603_1608Metric
C43: 75pF; C_0603_1608Metric
C44: 47µF; CP_Elec_6.3x5.4
JP1: Jumper_2_Bridged; PinHeader_1x02_P2.54mm_Vertical
L6: 10µH; L_Radial_D7.5mm_P3.50mm_Fastron_07P
R27: 470k; R_0603_1608Metric
R29, R31: 100k; R_0603_1608Metric
R30: 49.9; R_0603_1608Metric
R32: 10k; R_0603_1608Metric
R33: 3k3; R_0603_1608Metric
U3: TPS54308; SOT-23-6

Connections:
+5V: JP1.2 (B); also elsewhere on the board
+24V: C38.1, C39.1, C44.1, R27.1, U3.3 (VIN); also elsewhere on the board
/MCU_VoltageRegulator/VregFB: C43.2, R31.2, R32.1, U3.4 (FB)
/MCU_VoltageRegulator/VregSW: C40.2, L6.1, U3.2 (SW)
GND: C38.2, C39.2, C41.2, C42.2, C44.2, R29.2, R33.2, U3.1 (GND); also elsewhere on the board
unnamed: C43.1, R30.2, R31.1
unnamed: C41.1, C42.1, JP1.1 (A), L6.2, R30.1
unnamed: R32.2, R33.1
unnamed: C40.1, U3.6 (BOOT)
unnamed: R27.2, R29.1, U3.5 (EN)
